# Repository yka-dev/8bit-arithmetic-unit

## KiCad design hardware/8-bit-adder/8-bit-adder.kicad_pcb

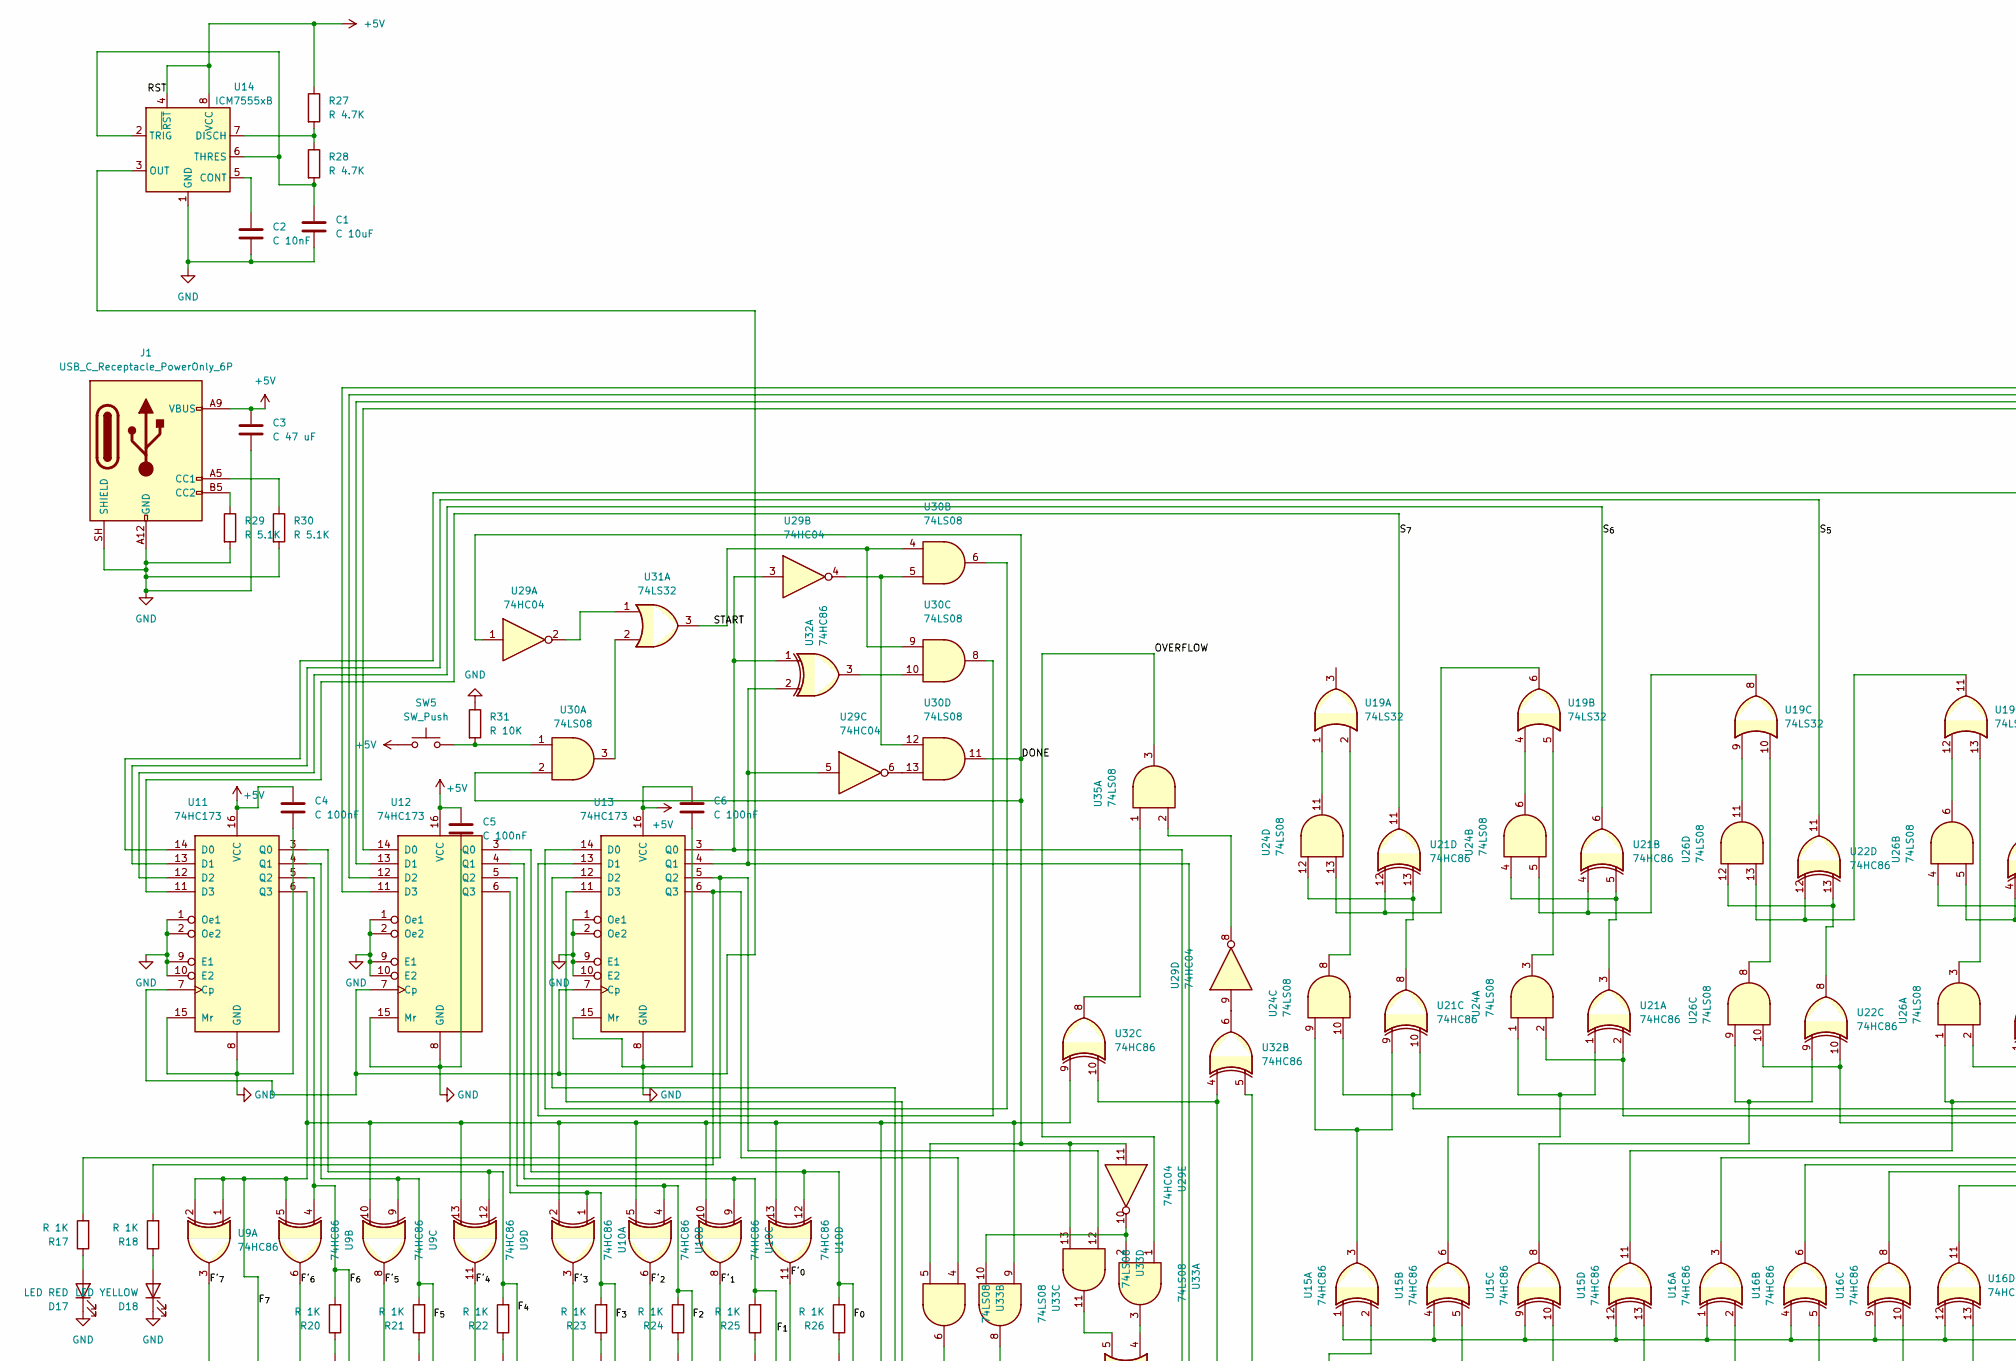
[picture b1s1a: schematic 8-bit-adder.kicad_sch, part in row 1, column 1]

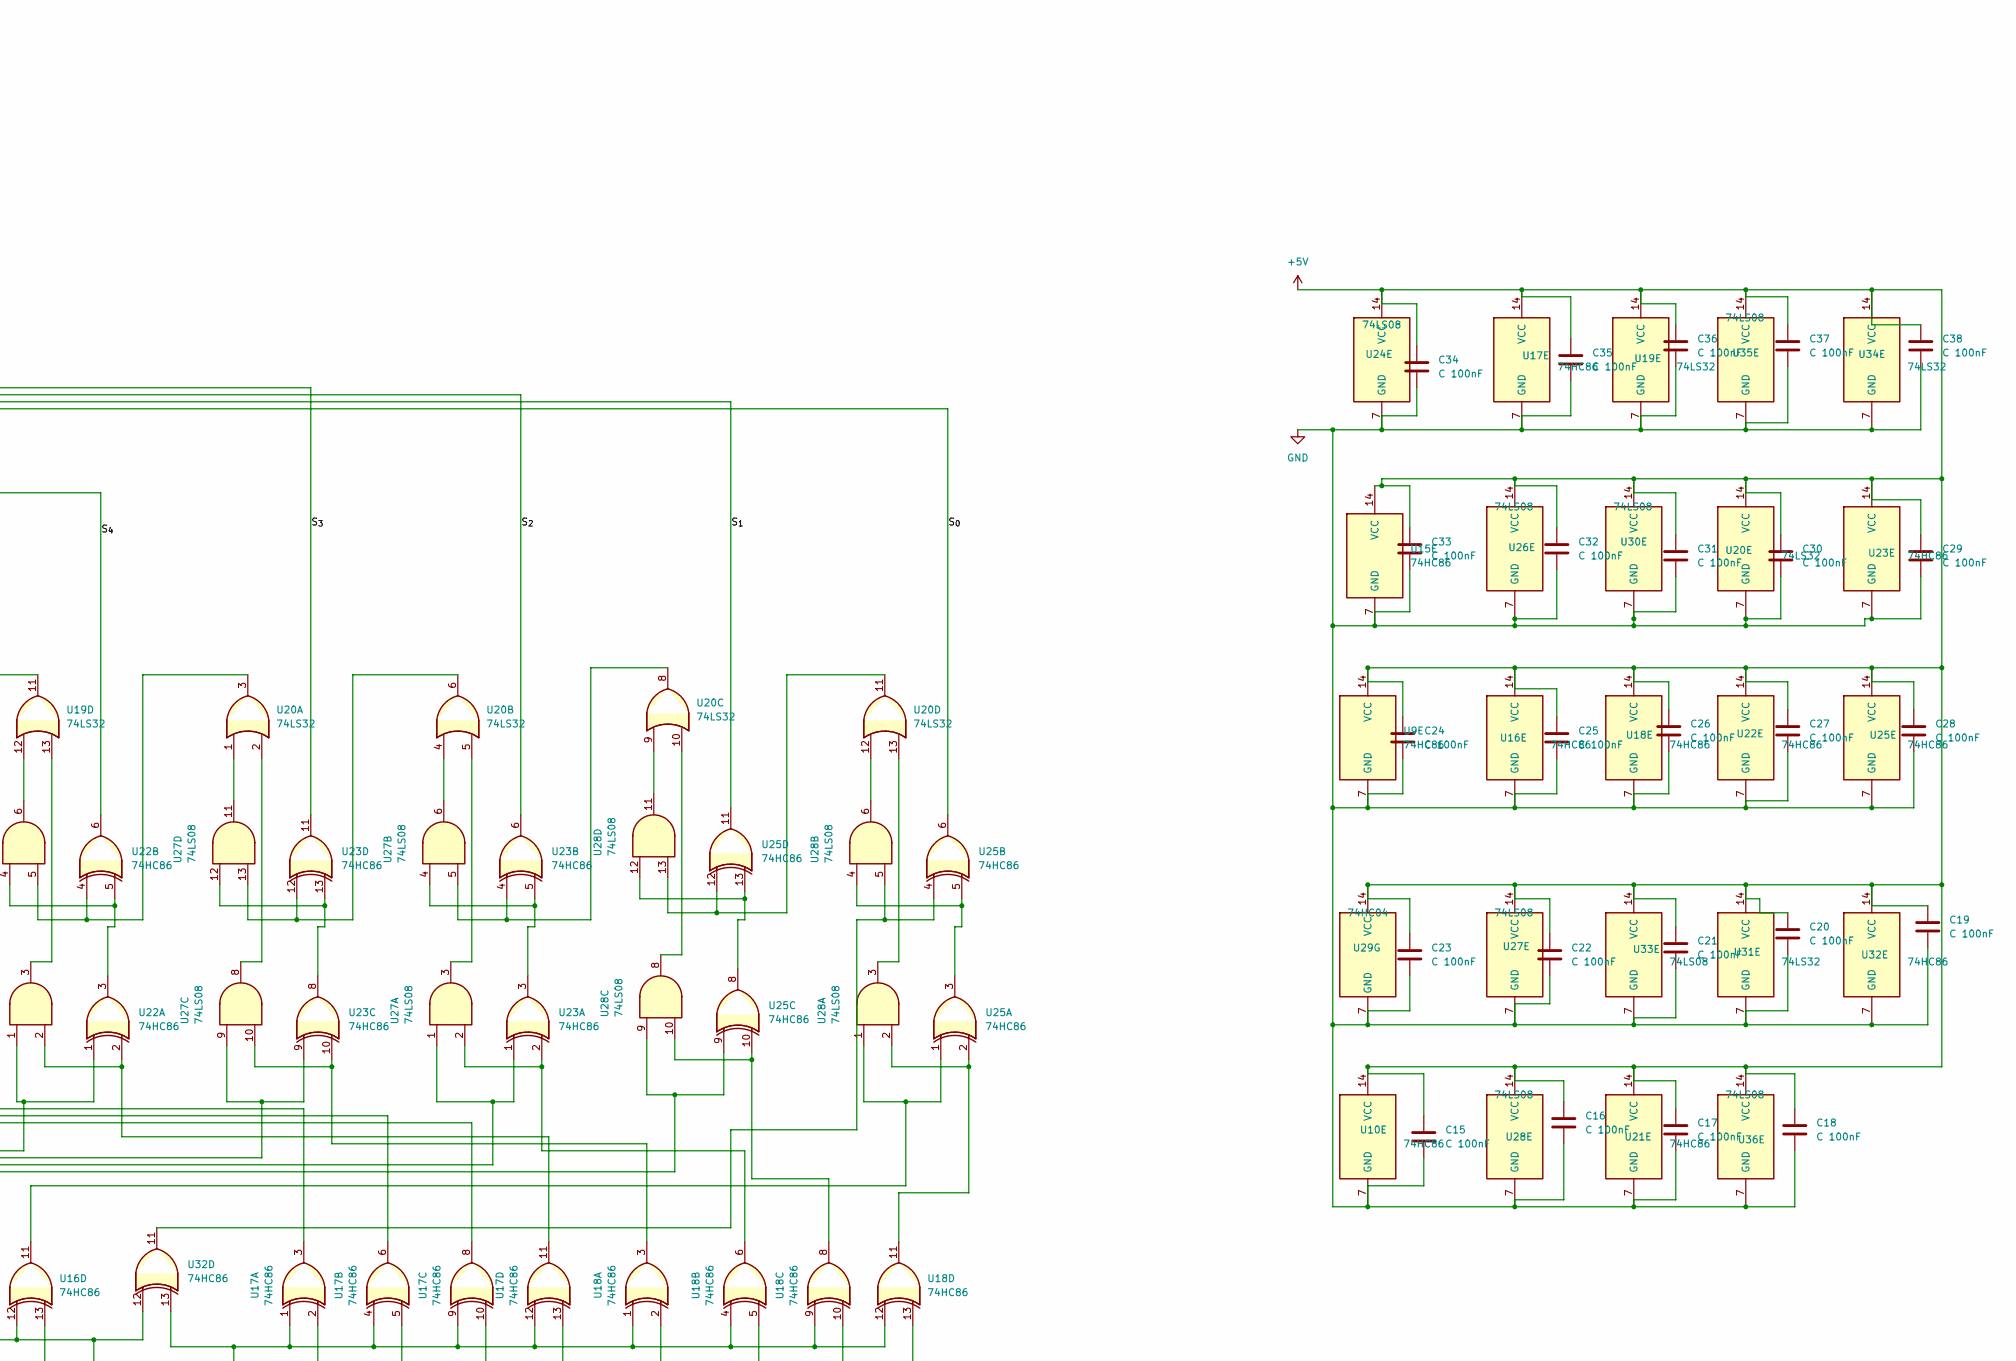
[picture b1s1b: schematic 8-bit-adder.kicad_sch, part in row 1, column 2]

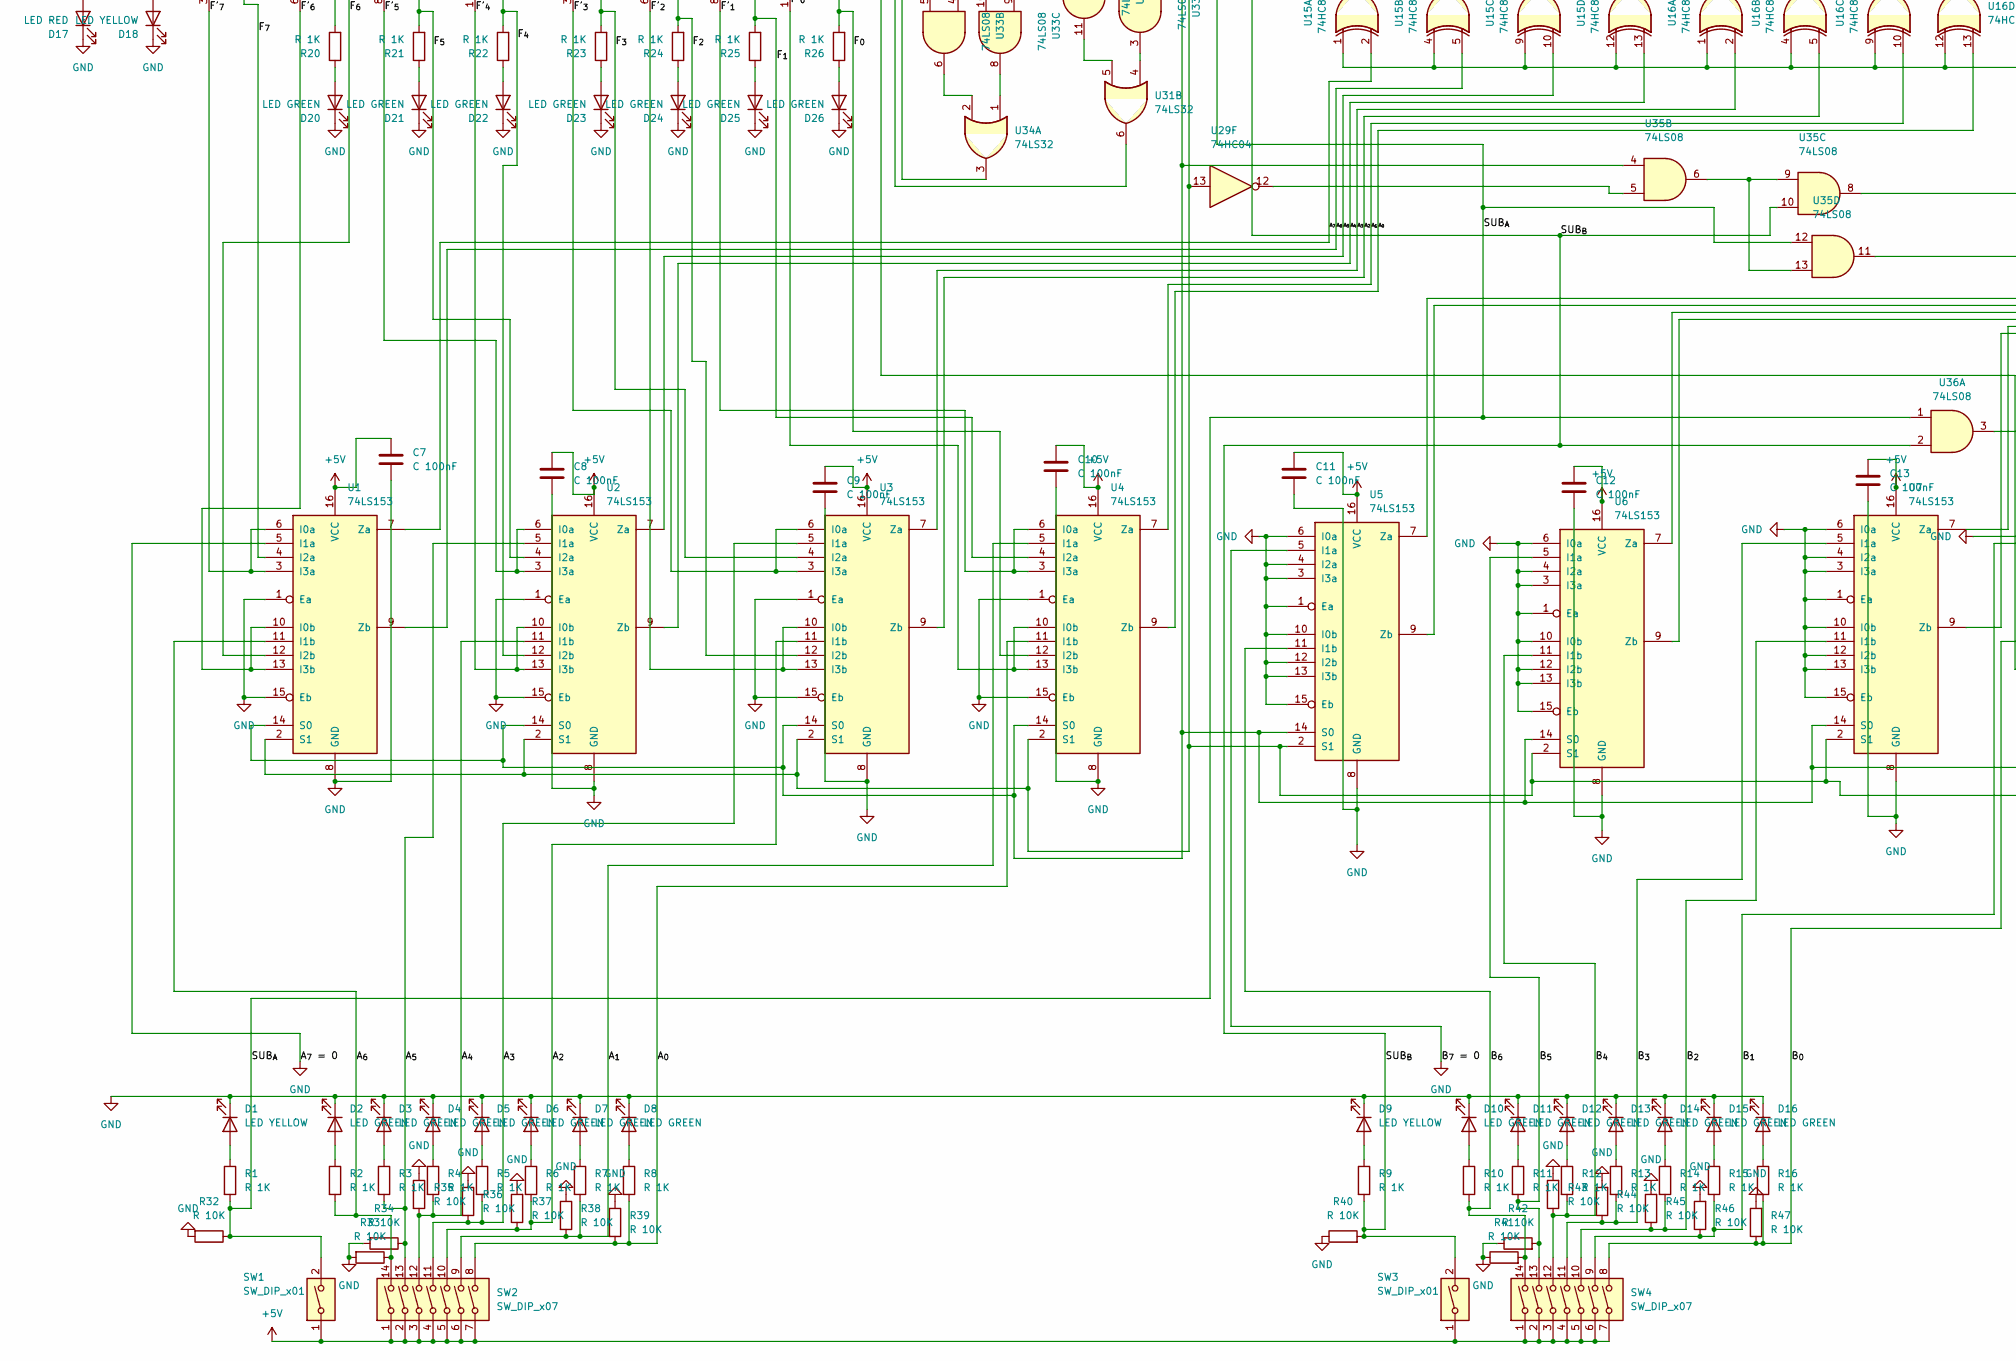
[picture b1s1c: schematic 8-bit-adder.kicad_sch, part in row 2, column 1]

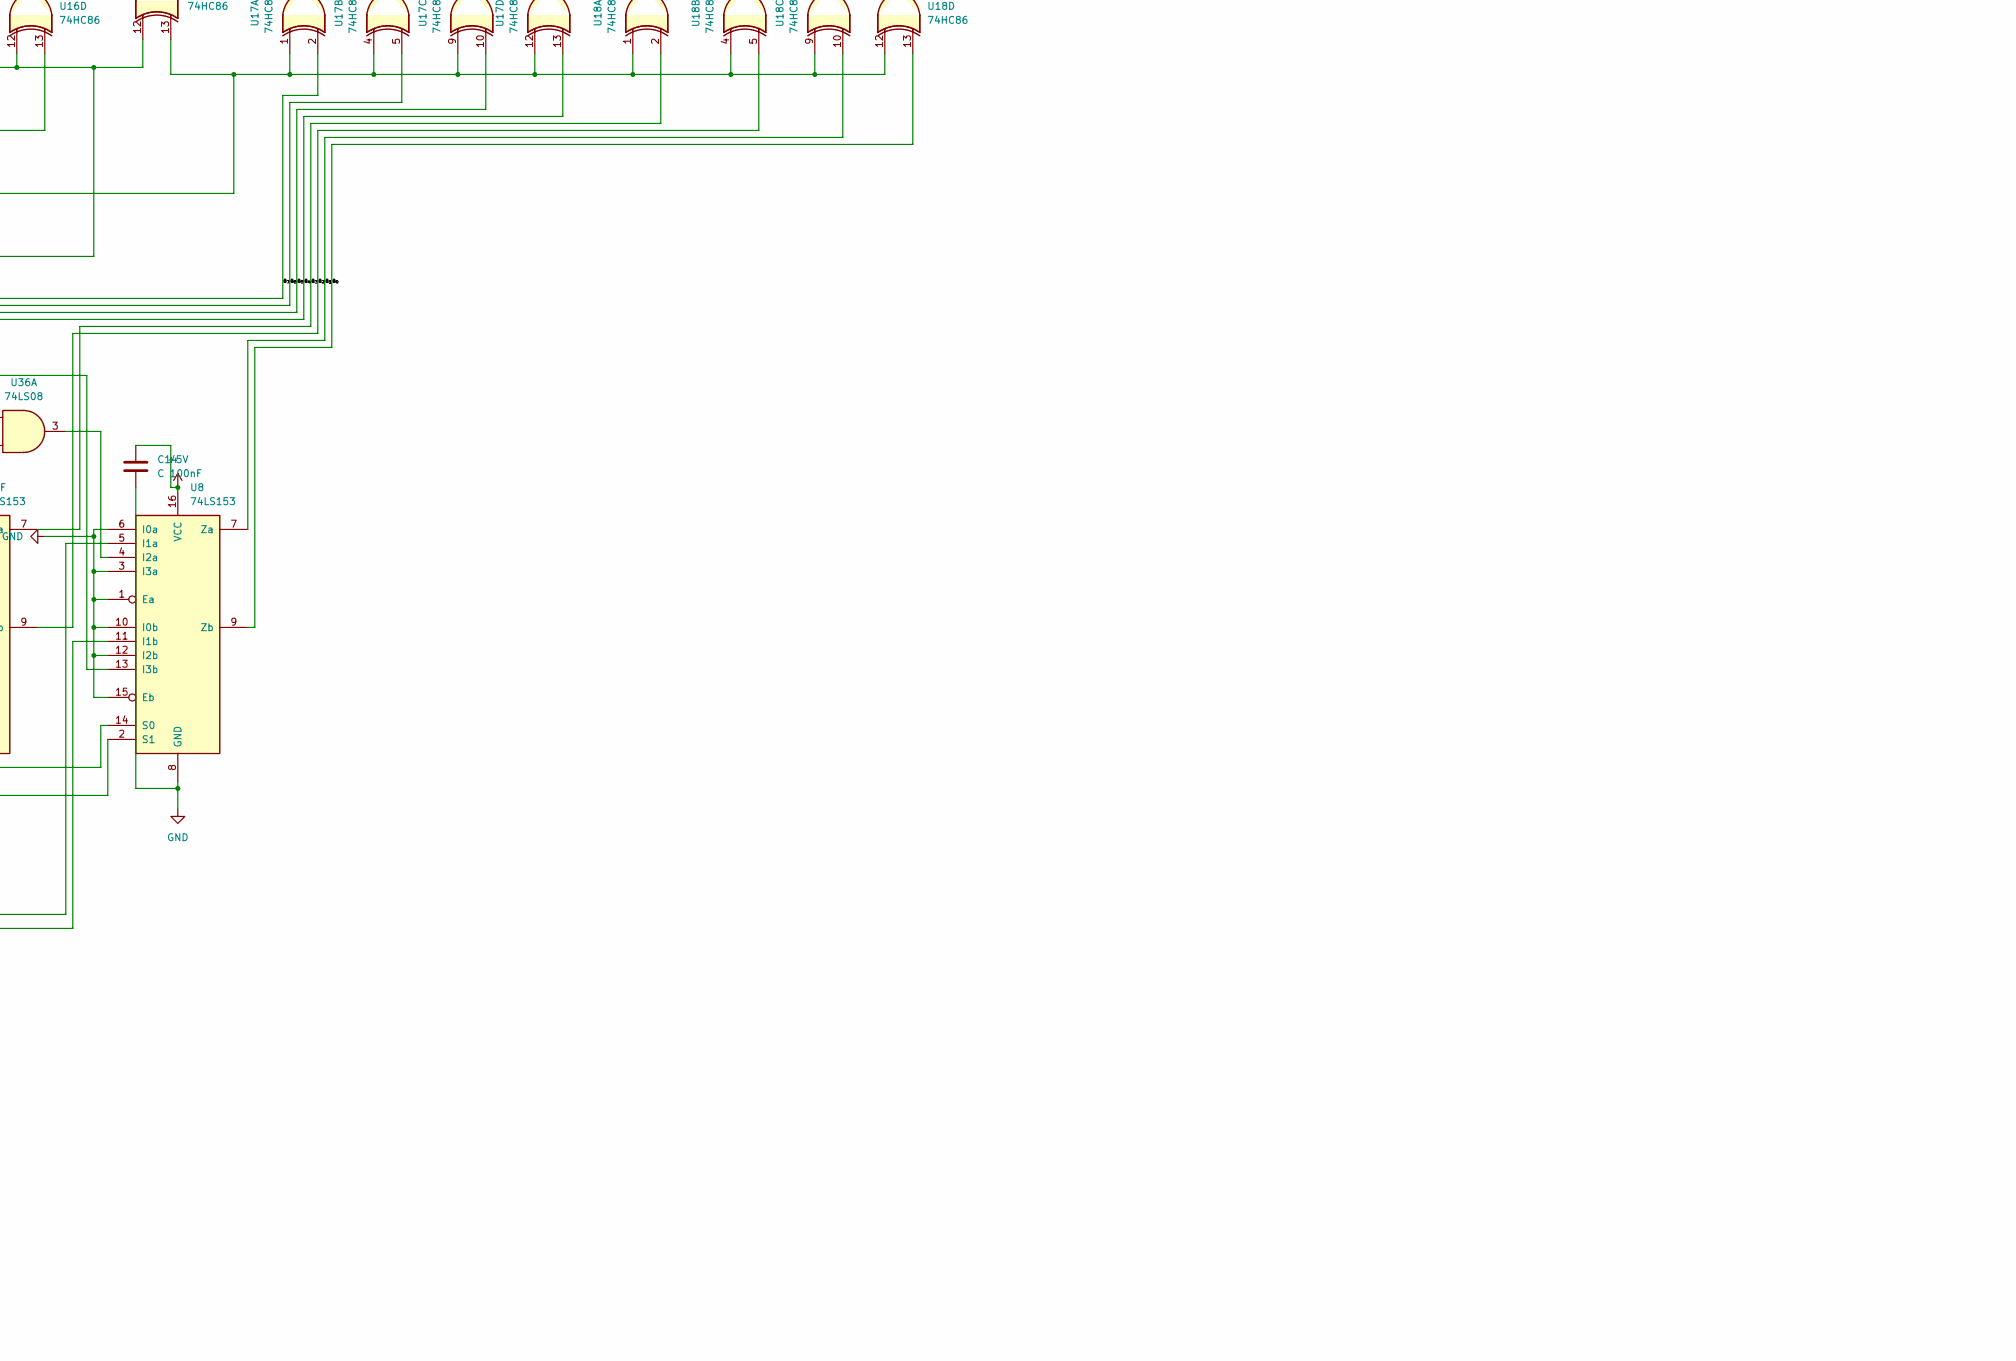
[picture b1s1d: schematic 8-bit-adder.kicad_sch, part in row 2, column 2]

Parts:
C1: C 10uF; C_Radial_D5.0mm_H5.0mm_P2.00mm
C2: C 10nF; C_Disc_D3.0mm_W1.6mm_P2.50mm
C3: C 47 uF; C_Radial_D5.0mm_H5.0mm_P2.00mm
C4, C5, C6, C7, C8, C9, C10, C11, C12, C13, C14, C15, C16, C17, C18, C19, C20, C21, C22, C23, C24, C25, C26, C27, C28, C29, C30, C31, C32, C33, C34, C35, C36, C37, C38: C 100nF; C_Disc_D3.0mm_W1.6mm_P2.50mm
D1, D9, D18: LED YELLOW; LED_D5.0mm
D2, D3, D4, D5, D6, D7, D8, D10, D11, D12, D13, D14, D15, D16, D20, D21, D22, D23, D24, D25, D26: LED GREEN; LED_D5.0mm
D17: LED RED; LED_D5.0mm
J1: USB_C_Receptacle_PowerOnly_6P; USB_C_Receptacle_GCT_USB4125-xx-x-0190_6P_TopMnt_Horizontal
R1, R2, R3, R4, R5, R6, R7, R8, R9, R10, R11, R12, R13, R14, R15, R16, R17, R18, R20, R21, R22, R23, R24, R25, R26: R 1K; R_Axial_DIN0207_L6.3mm_D2.5mm_P10.16mm_Horizontal
R27, R28: R 4.7K; R_Axial_DIN0207_L6.3mm_D2.5mm_P10.16mm_Horizontal
R29, R30: R 5.1K; R_Axial_DIN0207_L6.3mm_D2.5mm_P10.16mm_Horizontal
R31, R32, R33, R34, R35, R36, R37, R38, R39, R40, R41, R42, R43, R44, R45, R46, R47: R 10K; R_Axial_DIN0207_L6.3mm_D2.5mm_P10.16mm_Horizontal
SW1, SW3: SW_DIP_x01; SW_DIP_SPSTx01_Slide_9.78x4.72mm_W7.62mm_P2.54mm
SW2, SW4: SW_DIP_x07; SW_DIP_SPSTx07_Slide_9.78x19.96mm_W7.62mm_P2.54mm
SW5: SW_Push; SW_PUSH-12mm
U1, U2, U3, U4, U5, U6, U7, U8: 74LS153; DIP-16_W7.62mm_Socket
U9, U10, U15, U16, U17, U18, U21, U22, U23, U25, U32: 74HC86; DIP-14_W7.62mm_Socket
U11, U12, U13: 74HC173; DIP-16_W7.62mm_Socket
U14: ICM7555xB; DIP-8_W7.62mm_Socket
U19, U20, U31, U34: 74LS32; DIP-14_W7.62mm_Socket
U24, U26, U27, U28, U30, U33, U35, U36: 74LS08; DIP-14_W7.62mm_Socket
U29: 74HC04; DIP-14_W7.62mm_Socket

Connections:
+5V: C3.1, C4.1, C5.1, C6.1, C7.1, C8.1, C9.1, C10.1, C11.1, C12.1, C13.1, C14.1, C15.1, C16.1, C17.1, C18.1, C19.1, C20.1, C21.1, C22.1, C23.1, C24.1, C25.1, C26.1, C27.1, C28.1, C29.1, C30.1, C31.1, C32.1, C33.1, C34.1, C35.1, C36.1, C37.1, C38.1, J1.A9 (VBUS), J1.B9 (VBUS), R27.1, SW1.1, SW2.1, SW2.2, SW2.3, SW2.4, SW2.5, SW2.6, SW2.7, SW3.1, SW4.1, SW4.2, SW4.3, SW4.4, SW4.5, SW4.6, SW4.7, SW5.1, U1.16 (VCC), U2.16 (VCC), U3.16 (VCC), U4.16 (VCC), U5.16 (VCC), U6.16 (VCC), U7.16 (VCC), U8.16 (VCC), U9.14 (VCC), U10.14 (VCC), U11.16 (VCC), U12.16 (VCC), U13.16 (VCC), U14.4 (~RST), U14.8 (VCC), U15.14 (VCC), U16.14 (VCC), U17.14 (VCC), U18.14 (VCC), U19.14 (VCC), U20.14 (VCC), U21.14 (VCC), U22.14 (VCC), U23.14 (VCC), U24.14 (VCC), U25.14 (VCC), U26.14 (VCC), U27.14 (VCC), U28.14 (VCC), U29.14 (VCC), U30.14 (VCC), U31.14 (VCC), U32.14 (VCC), U33.14 (VCC), U34.14 (VCC), U35.14 (VCC), U36.14 (VCC)
/A_{0}: R8.2, R39.2, SW2.8, U4.9 (Zb), U4.11 (I1b), U16.13
/A_{1}: R7.2, R38.2, SW2.9, U4.5 (I1a), U4.7 (Za), U16.10
/A_{2}: R6.2, R37.1, SW2.10, U3.9 (Zb), U3.11 (I1b), U16.5
/A_{3}: R5.2, R36.2, SW2.11, U3.5 (I1a), U3.7 (Za), U16.2
/A_{4}: R4.2, R35.2, SW2.12, U2.9 (Zb), U2.11 (I1b), U15.13
/A_{5}: R3.2, R34.1, SW2.13, U2.5 (I1a), U2.7 (Za), U15.10
/A_{6}: R2.2, R33.1, SW2.14, U1.9 (Zb), U1.11 (I1b), U15.5
/A_{7}: U1.7 (Za), U15.2
/B_{0}: R16.2, R47.1, SW4.8, U8.9 (Zb), U8.11 (I1b), U18.13
/B_{1}: R15.2, R46.1, SW4.9, U8.5 (I1a), U8.7 (Za), U18.10
/B_{2}: R14.2, R45.1, SW4.10, U7.9 (Zb), U7.11 (I1b), U18.5
/B_{3}: R13.2, R44.1, SW4.11, U7.5 (I1a), U7.7 (Za), U18.2
/B_{4}: R12.2, R43.1, SW4.12, U6.9 (Zb), U6.11 (I1b), U17.13
/B_{5}: R11.2, R42.2, SW4.13, U6.5 (I1a), U6.7 (Za), U17.10
/B_{6}: R10.2, R41.2, SW4.14, U5.9 (Zb), U5.11 (I1b), U17.5
/B_{7}: U5.7 (Za), U17.2
/DONE: U29.1, U29.11, U30.2, U30.11, U33.5, U33.13
/F'_{1}: U4.3 (I3a), U4.6 (I0a), U10.8
/F'_{2}: U3.10 (I0b), U3.13 (I3b), U10.6
/F'_{3}: U3.3 (I3a), U3.6 (I0a), U10.3
/F'_{4}: U2.10 (I0b), U2.13 (I3b), U9.11
/F'_{5}: U2.3 (I3a), U2.6 (I0a), U9.8
/F'_{6}: U1.10 (I0b), U1.13 (I3b), U9.6
/F'_{7}: U1.3 (I3a), U1.6 (I0a), U9.3
/F_{0}: R26.2, U4.12 (I2b), U10.12, U12.3 (Q0)
/F_{1}: R25.2, U4.4 (I2a), U10.9, U12.4 (Q1)
/F_{2}: R24.2, U3.12 (I2b), U10.4, U12.5 (Q2)
/F_{3}: R23.2, U3.4 (I2a), U10.1, U12.6 (Q3)
/F_{4}: R22.2, U2.12 (I2b), U9.12, U11.3 (Q0)
/F_{5}: R21.2, U2.4 (I2a), U9.9, U11.4 (Q1)
/F_{6}: R20.2, U1.12 (I2b), U9.4, U11.5 (Q2)
/F_{7}: U1.4 (I2a), U8.13 (I3b), U9.1, U9.2, U9.5, U9.10, U9.13, U10.2, U10.5, U10.10, U10.13, U11.6 (Q3), U32.9, U33.9
/OVERFLOW: U33.1, U35.3
/START: U30.4, U30.9, U31.3
/SUB_{A}: R1.2, R32.1, SW1.2, U32.4, U32.10, U35.12, U36.1
/SUB_{B}: R9.2, R40.2, SW3.2, U32.5, U35.10, U36.2
/S_{0}: U12.14 (D0), U25.6
/S_{1}: U12.13 (D1), U25.11
/S_{2}: U12.12 (D2), U23.6
/S_{3}: U12.11 (D3), U23.11
/S_{4}: U11.14 (D0), U22.6
/S_{5}: U11.13 (D1), U22.11
/S_{6}: U11.12 (D2), U21.6
/S_{7}: U11.11 (D3), U21.11
GND: C1.2, C2.2, C3.2, C4.2, C5.2, C6.2, C7.2, C8.2, C9.2, C10.2, C11.2, C12.2, C13.2, C14.2, C15.2, C16.2, C17.2, C18.2, C19.2, C20.2, C21.2, C22.2, C23.2, C24.2, C25.2, C26.2, C27.2, C28.2, C29.2, C30.2, C31.2, C32.2, C33.2, C34.2, C35.2, C36.2, C37.2, C38.2, D1.1 (K), D2.1 (K), D3.1 (K), D4.1 (K), D5.1 (K), D6.1 (K), D7.1 (K), D8.1 (K), D9.1 (K), D10.1 (K), D11.1 (K), D12.1 (K), D13.1 (K), D14.1 (K), D15.1 (K), D16.1 (K), D17.1 (K), D18.1 (K), D20.1 (K), D21.1 (K), D22.1 (K), D23.1 (K), D24.1 (K), D25.1 (K), D26.1 (K), J1.A12 (GND), J1.B12 (GND), J1.SH (SHIELD), R29.2, R30.2, R31.1, R32.2, R33.2, R34.2, R35.1, R36.1, R37.2, R38.1, R39.1, R40.1, R41.1, R42.1, R43.2, R44.2, R45.2, R46.2, R47.2, U1.1 (Ea), U1.5 (I1a), U1.8 (GND), U1.15 (Eb), U2.1 (Ea), U2.8 (GND), U2.15 (Eb), U3.1 (Ea), U3.8 (GND), U3.15 (Eb), U4.1 (Ea), U4.8 (GND), U4.15 (Eb), U5.1 (Ea), U5.3 (I3a), U5.4 (I2a), U5.5 (I1a), U5.6 (I0a), U5.8 (GND), U5.10 (I0b), U5.12 (I2b), U5.13 (I3b), U5.15 (Eb), U6.1 (Ea), U6.3 (I3a), U6.4 (I2a), U6.6 (I0a), U6.8 (GND), U6.10 (I0b), U6.12 (I2b), U6.13 (I3b), U6.15 (Eb), U7.1 (Ea), U7.3 (I3a), U7.4 (I2a), U7.6 (I0a), U7.8 (GND), U7.10 (I0b), U7.12 (I2b), U7.13 (I3b), U7.15 (Eb), U8.1 (Ea), U8.3 (I3a), U8.6 (I0a), U8.8 (GND), U8.10 (I0b), U8.12 (I2b), U8.15 (Eb), U9.7 (GND), U10.7 (GND), U11.1 (Oe1), U11.2 (Oe2), U11.8 (GND), U11.9 (E1), U11.10 (E2), U11.15 (Mr), U12.1 (Oe1), U12.2 (Oe2), U12.8 (GND), U12.9 (E1), U12.10 (E2), U12.15 (Mr), U13.1 (Oe1), U13.2 (Oe2), U13.8 (GND), U13.9 (E1), U13.10 (E2), U13.15 (Mr), U14.1 (GND), U15.7 (GND), U16.7 (GND), U17.7 (GND), U18.7 (GND), U19.7 (GND), U20.7 (GND), U21.7 (GND), U22.7 (GND), U23.7 (GND), U24.7 (GND), U25.7 (GND), U26.7 (GND), U27.7 (GND), U28.7 (GND), U29.7 (GND), U30.7 (GND), U31.7 (GND), U32.7 (GND), U33.7 (GND), U34.7 (GND), U35.7 (GND), U36.7 (GND)
unnamed: D1.2 (A), R1.1
unnamed: D2.2 (A), R2.1
unnamed: D3.2 (A), R3.1
unnamed: D4.2 (A), R4.1
unnamed: D5.2 (A), R5.1
unnamed: D6.2 (A), R6.1
unnamed: D7.2 (A), R7.1
unnamed: D8.2 (A), R8.1
unnamed: D9.2 (A), R9.1
unnamed: D10.2 (A), R10.1
unnamed: D11.2 (A), R11.1
unnamed: D12.2 (A), R12.1
unnamed: D13.2 (A), R13.1
unnamed: D14.2 (A), R14.1
unnamed: D15.2 (A), R15.1
unnamed: D16.2 (A), R16.1
unnamed: D17.2 (A), R17.1
unnamed: D18.2 (A), R18.1
unnamed: D20.2 (A), R20.1
unnamed: D21.2 (A), R21.1
unnamed: D22.2 (A), R22.1
unnamed: D23.2 (A), R23.1
unnamed: D24.2 (A), R24.1
unnamed: D25.2 (A), R25.1
unnamed: D26.2 (A), R26.1
unnamed: J1.A5 (CC1), R30.1
unnamed: J1.B5 (CC2), R29.1
unnamed: R31.2, SW5.2, U30.1
unnamed: U1.14 (S0), U2.14 (S0), U3.14 (S0), U4.14 (S0), U5.14 (S0), U6.14 (S0), U7.14 (S0), U8.14 (S0), U13.3 (Q0), U29.3, U32.1, U35.4
unnamed: U1.2 (S1), U2.2 (S1), U3.2 (S1), U4.2 (S1), U5.2 (S1), U6.2 (S1), U7.2 (S1), U8.2 (S1), U13.4 (Q1), U29.5, U29.13, U32.2
unnamed: U4.10 (I0b), U4.13 (I3b), U10.11
unnamed: U8.4 (I2a), U36.3
unnamed: U11.7 (Cp), U12.7 (Cp), U13.7 (Cp), U14.3 (OUT)
unnamed: U13.14 (D0), U30.6
unnamed: U13.13 (D1), U30.8
unnamed: U13.12 (D2), U31.6
unnamed: U13.11 (D3), U34.3
unnamed: R17.2, U13.5 (Q2), U33.12
unnamed: R18.2, U13.6 (Q3), U33.4
unnamed: C2.1, U14.5 (CONT)
unnamed: R27.2, R28.1, U14.7 (DISCH)
unnamed: C1.1, R28.2, U14.2 (TRIG), U14.6 (THRES)
unnamed: U15.1, U15.4, U15.9, U15.12, U16.1, U16.4, U16.9, U16.12, U32.12, U35.11
unnamed: U15.3, U21.9, U24.9
unnamed: U15.6, U21.1, U24.1
unnamed: U15.8, U22.9, U26.9
unnamed: U15.11, U22.1, U26.1
unnamed: U16.3, U23.9, U27.9
unnamed: U16.6, U23.1, U27.1
unnamed: U16.8, U25.9, U28.9
unnamed: U16.11, U25.1, U28.1
unnamed: U17.1, U17.4, U17.9, U17.12, U18.1, U18.4, U18.9, U18.12, U32.13, U35.8
unnamed: U17.3, U21.10, U24.10
unnamed: U17.6, U21.2, U24.2
unnamed: U17.8, U22.10, U26.10
unnamed: U17.11, U22.2, U26.2
unnamed: U18.3, U23.10, U27.10
unnamed: U18.6, U23.2, U27.2
unnamed: U18.8, U25.10, U28.10
unnamed: U18.11, U25.2, U28.2
unnamed: U19.1, U24.11
unnamed: U19.2, U24.8
unnamed: U19.4, U24.6
unnamed: U19.5, U24.3
unnamed: U19.6, U21.12, U24.13
unnamed: U19.8, U21.4, U24.5
unnamed: U19.9, U26.11
unnamed: U19.10, U26.8
unnamed: U19.11, U22.12, U26.13
unnamed: U19.12, U26.6
unnamed: U19.13, U26.3
unnamed: U20.1, U27.11
unnamed: U20.2, U27.8
unnamed: U20.3, U22.4, U26.5
unnamed: U20.4, U27.6
unnamed: U20.5, U27.3
unnamed: U20.6, U23.12, U27.13
unnamed: U20.8, U23.4, U27.5
unnamed: U20.9, U28.11
unnamed: U20.10, U28.8
unnamed: U20.11, U25.12, U28.13
unnamed: U20.12, U28.6
unnamed: U20.13, U28.3
unnamed: U21.3, U21.5, U24.4
unnamed: U21.8, U21.13, U24.12
unnamed: U22.3, U22.5, U26.4
unnamed: U22.8, U22.13, U26.12
unnamed: U23.3, U23.5, U27.4
unnamed: U23.8, U23.13, U27.12
unnamed: U25.3, U25.5, U28.4
unnamed: U25.4, U28.5, U32.11
unnamed: U25.8, U25.13, U28.12
unnamed: U29.2, U31.1
unnamed: U29.4, U30.5, U30.12
unnamed: U29.6, U30.13
unnamed: U29.8, U35.2
unnamed: U29.9, U32.6
unnamed: U29.10, U33.2, U33.10
unnamed: U29.12, U35.5
unnamed: U30.3, U31.2
unnamed: U30.10, U32.3
unnamed: U31.4, U33.3
unnamed: U31.5, U33.11
unnamed: U32.8, U35.1
unnamed: U33.6, U34.2
unnamed: U33.8, U34.1
unnamed: U35.6, U35.9, U35.13

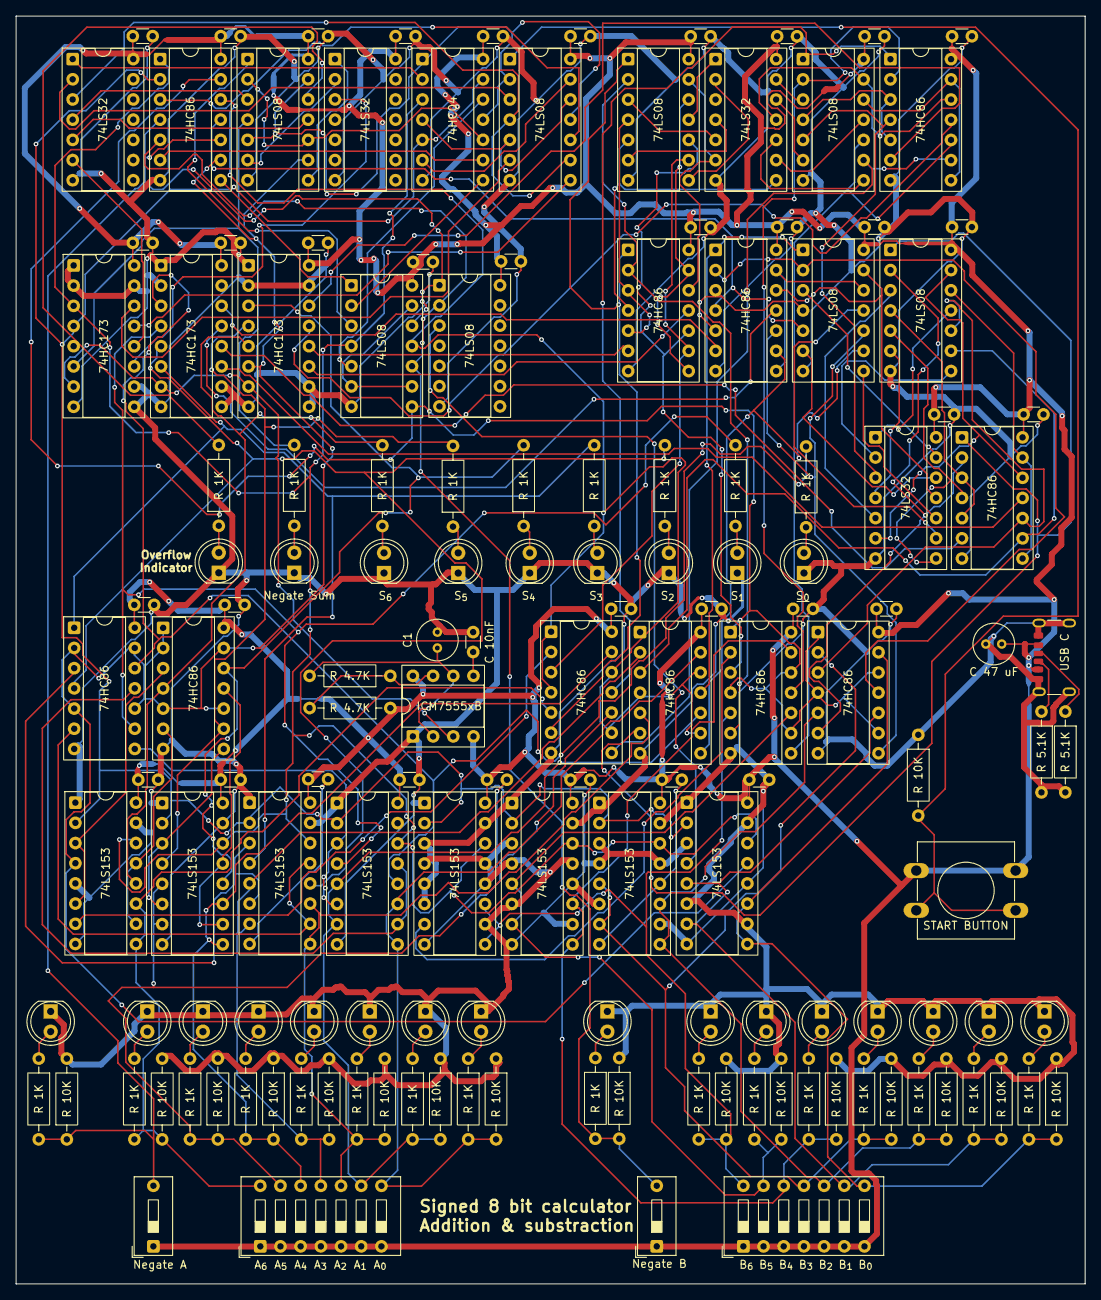
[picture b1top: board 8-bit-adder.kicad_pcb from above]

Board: 2 copper layers, 134.5 x 159.5 mm, 151 parts (0 on the bottom side), 153 nets.

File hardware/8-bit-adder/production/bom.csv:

Designator,Footprint,Quantity,Value,LCSC Part #
C1,C_Radial_D5.0mm_H5.0mm_P2.00mm,1,C 10uF,
"C10, C11, C12, C13, C14, C15, C16, C17, C18, C19, C20, C21, C22, C23, C24, C25, C26, C27, C28, C29, C30, C31, C32, C33, C34, C35, C36, C37, C38, C4, C5, C6, C7, C8, C9",C_Disc_D3.0mm_W1.6mm_P2.50mm,35,C 100nF,
C2,C_Disc_D3.0mm_W1.6mm_P2.50mm,1,C 10nF,
C3,C_Radial_D5.0mm_H5.0mm_P2.00mm,1,C 47 uF,
"D1, D18, D9",LED_D5.0mm,3,LED YELLOW,
"D10, D11, D12, D13, D14, D15, D16, D2, D20, D21, D22, D23, D24, D25, D26, D3, D4, D5, D6, D7, D8",LED_D5.0mm,21,LED GREEN,
D17,LED_D5.0mm,1,LED RED,
J1,USB_C_Receptacle_GCT_USB4125-xx-x-0190_6P_TopMnt_Horizontal,1,USB_C_Receptacle_PowerOnly_6P,
"R1, R10, R11, R12, R13, R14, R15, R16, R17, R18, R2, R20, R21, R22, R23, R24, R25, R26, R3, R4, R5, R6, R7, R8, R9",R_Axial_DIN0207_L6.3mm_D2.5mm_P10.16mm_Horizontal,25,R 1K,
"R27, R28",R_Axial_DIN0207_L6.3mm_D2.5mm_P10.16mm_Horizontal,2,R 4.7K,
"R29, R30",R_Axial_DIN0207_L6.3mm_D2.5mm_P10.16mm_Horizontal,2,R 5.1K,
"R31, R32, R33, R34, R35, R36, R37, R38, R39, R40, R41, R42, R43, R44, R45, R46, R47",R_Axial_DIN0207_L6.3mm_D2.5mm_P10.16mm_Horizontal,17,R 10K,
"SW1, SW3",SW_DIP_SPSTx01_Slide_9.78x4.72mm_W7.62mm_P2.54mm,2,SW_DIP_x01,
"SW2, SW4",SW_DIP_SPSTx07_Slide_9.78x19.96mm_W7.62mm_P2.54mm,2,SW_DIP_x07,
SW5,SW_PUSH-12mm,1,SW_Push,
"U1, U2, U3, U4, U5, U6, U7, U8",DIP-16_W7.62mm_Socket,8,74LS153,
"U10, U15, U16, U17, U18, U21, U22, U23, U25, U32, U9",DIP-14_W7.62mm_Socket,11,74HC86,
"U11, U12, U13",DIP-16_W7.62mm_Socket,3,74HC173,
U14,DIP-8_W7.62mm_Socket,1,ICM7555xB,
"U19, U20, U31, U34",DIP-14_W7.62mm_Socket,4,74LS32,
"U24, U26, U27, U28, U30, U33, U35, U36",DIP-14_W7.62mm_Socket,8,74LS08,
U29,DIP-14_W7.62mm_Socket,1,74HC04,
